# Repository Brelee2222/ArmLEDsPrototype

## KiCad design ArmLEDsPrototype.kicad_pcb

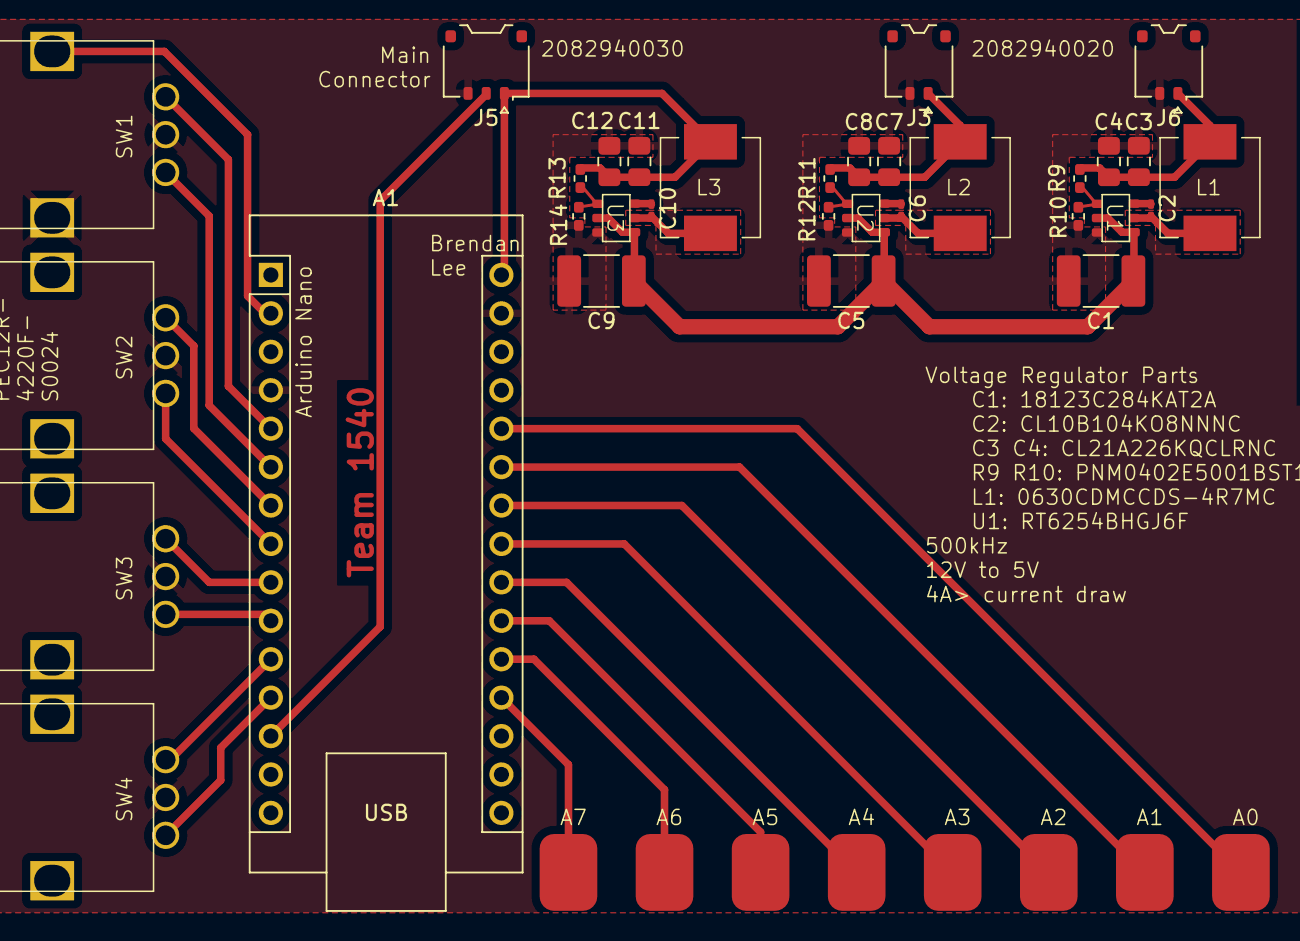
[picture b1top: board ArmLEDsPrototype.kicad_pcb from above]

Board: 2 copper layers, 33 parts (0 on the bottom side), 32 nets.

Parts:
A1: Arduino_Nano_Every; Arduino_Nano
C1, C5, C9: C; C_1812_4532Metric_Pad1.57x3.40mm_HandSolder
C2, C6, C10: C; C_0201_0603Metric_Pad0.64x0.40mm_HandSolder
C3, C4, C7, C8, C11, C12: C; C_0805_2012Metric_Pad1.18x1.45mm_HandSolder
J1: Conn_01x08; 8Pad
J3, J6: Conn_01x02; Molex_Pico-EZmate_78171-0002_1x02-1MP_P1.20mm_Vertical
J5: Conn_01x03; Molex_Pico-EZmate_78171-0003_1x03-1MP_P1.20mm_Vertical
L1, L2, L3: L; 4r7007
R9, R10, R11, R12, R13, R14: R; R_0402_1005Metric_Pad0.72x0.64mm_HandSolder
SW1: RotaryEncoder_Switch; RotaryEncoder
SW2, SW3, SW4: RotaryEncoder
U1, U2, U3: RT6254A

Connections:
+9V: C1.1, C5.1, C9.1, U1.2 (EN), U1.4 (VIN), U2.2 (EN), U2.4 (VIN), U3.2 (EN), U3.4 (VIN)
/5V#1: C3.1, C4.1, J6.1, L1.2, R9.1
/5V#2: C7.1, C8.1, J3.1, L2.2, R11.1
/5V#3: A1.30 (VIN), C11.1, C12.1, J5.1, L3.2, R13.1
/Controller/Input1A: A1.6 (D3), SW1.A
/Controller/Input1B: A1.5 (D2), SW1.B
/Controller/Input2A: A1.8 (D5), SW2.A
/Controller/Input2B: A1.7 (D4), SW2.B
/Controller/Input3A: A1.10 (D7), SW3.A
/Controller/Input3B: A1.9 (D6), SW3.B
/Controller/Input4A: A1.12 (D9), SW4.A
/Controller/Input4B: A1.11 (D8), SW4.B
/Controller/InputS: A1.2 (RX1), SW1.S2
/LED_S: A1.13 (D10), J5.2
GND: A1.4 (GND), A1.29 (GND), C1.2, C3.2, C4.2, C5.2, C7.2, C8.2, C9.2, C11.2, C12.2, J3.2, J5.3, J6.2, R10.2, R12.2, R14.2, SW1.C, SW1.S1, SW2.C, SW3.C, SW4.C, U1.3 (GND), U2.3 (GND), U3.3 (GND)
unnamed: A1.19 (A0), J1.1
unnamed: A1.20 (A1), J1.2
unnamed: A1.21 (A2), J1.3
unnamed: A1.22 (A3), J1.4
unnamed: A1.25 (A6), J1.7
unnamed: A1.26 (A7), J1.8
unnamed: A1.24 (SCL/A5), J1.6
unnamed: A1.23 (SDA/A4), J1.5
unnamed: C2.1, U1.6 (BOOT)
unnamed: R9.2, R10.1, U1.1 (FB)
unnamed: C2.2, L1.1, U1.5 (LX)
unnamed: C6.1, U2.6 (BOOT)
unnamed: R11.2, R12.1, U2.1 (FB)
unnamed: C6.2, L2.1, U2.5 (LX)
unnamed: C10.1, U3.6 (BOOT)
unnamed: R13.2, R14.1, U3.1 (FB)
unnamed: C10.2, L3.1, U3.5 (LX)

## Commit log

2024-06-26 Added connections
2024-06-27 Added Probably Voltage Regulator Parts
2024-07-05 Added components
2024-07-05 Added parts
2024-07-05 Added resistor parts + inductor
2024-07-05 Changed indcutor
2024-07-05 Making PCB
2024-07-06 Replaced switch & pots with rotaries
2024-07-06 Added information
2024-07-06 Fixed wiring mistake + information
